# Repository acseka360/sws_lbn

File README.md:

# Lora Battery Node
## Solder WorkShop - *Advanced Track*

### PCB

Check out the PCB files with [Kicad 10](https://www.kicad.org/)

- Open the kicad\_pro project file
- Look at the schematic with the "Schematic Editor"
- Proceed to the "PCB editor" and push Alt-F3 to get into the 3D viewer

### Assembly

The interactive [BOM
webpage](https://htmlpreview.github.io/?https://github.com/acseka360/sws_lbn/blob/master/bom/ibom.html)
helps during assembly. You can mark components placed and check their exact
types.

### Bootloader

Initially a [J-Link](https://www.segger.com/products/debug-probes/j-link/) or
equivalent swd flasher is needed to load the bootloader on the virgin chip.

Use the *pca10056* type from the
[Adafruit](https://github.com/adafruit/Adafruit_nRF52_Bootloader/releases) repo.

### Firmware

You will need [PlatformIO](https://platformio.org/) to compile and install it.

First the bootstrapping firmware is needed, to set the IO voltages to 3.3V
permanently from the default 1.8V.

Then you can get the upstream
[Meshtastic](https://github.com/meshtastic/firmware) repo, that you should merge 
into the firmware folder, where our custom variant files already describe the 
board.

### 3D printed case

[Freecad 1.1](https://www.freecad.org/) made the 3d printed case files.

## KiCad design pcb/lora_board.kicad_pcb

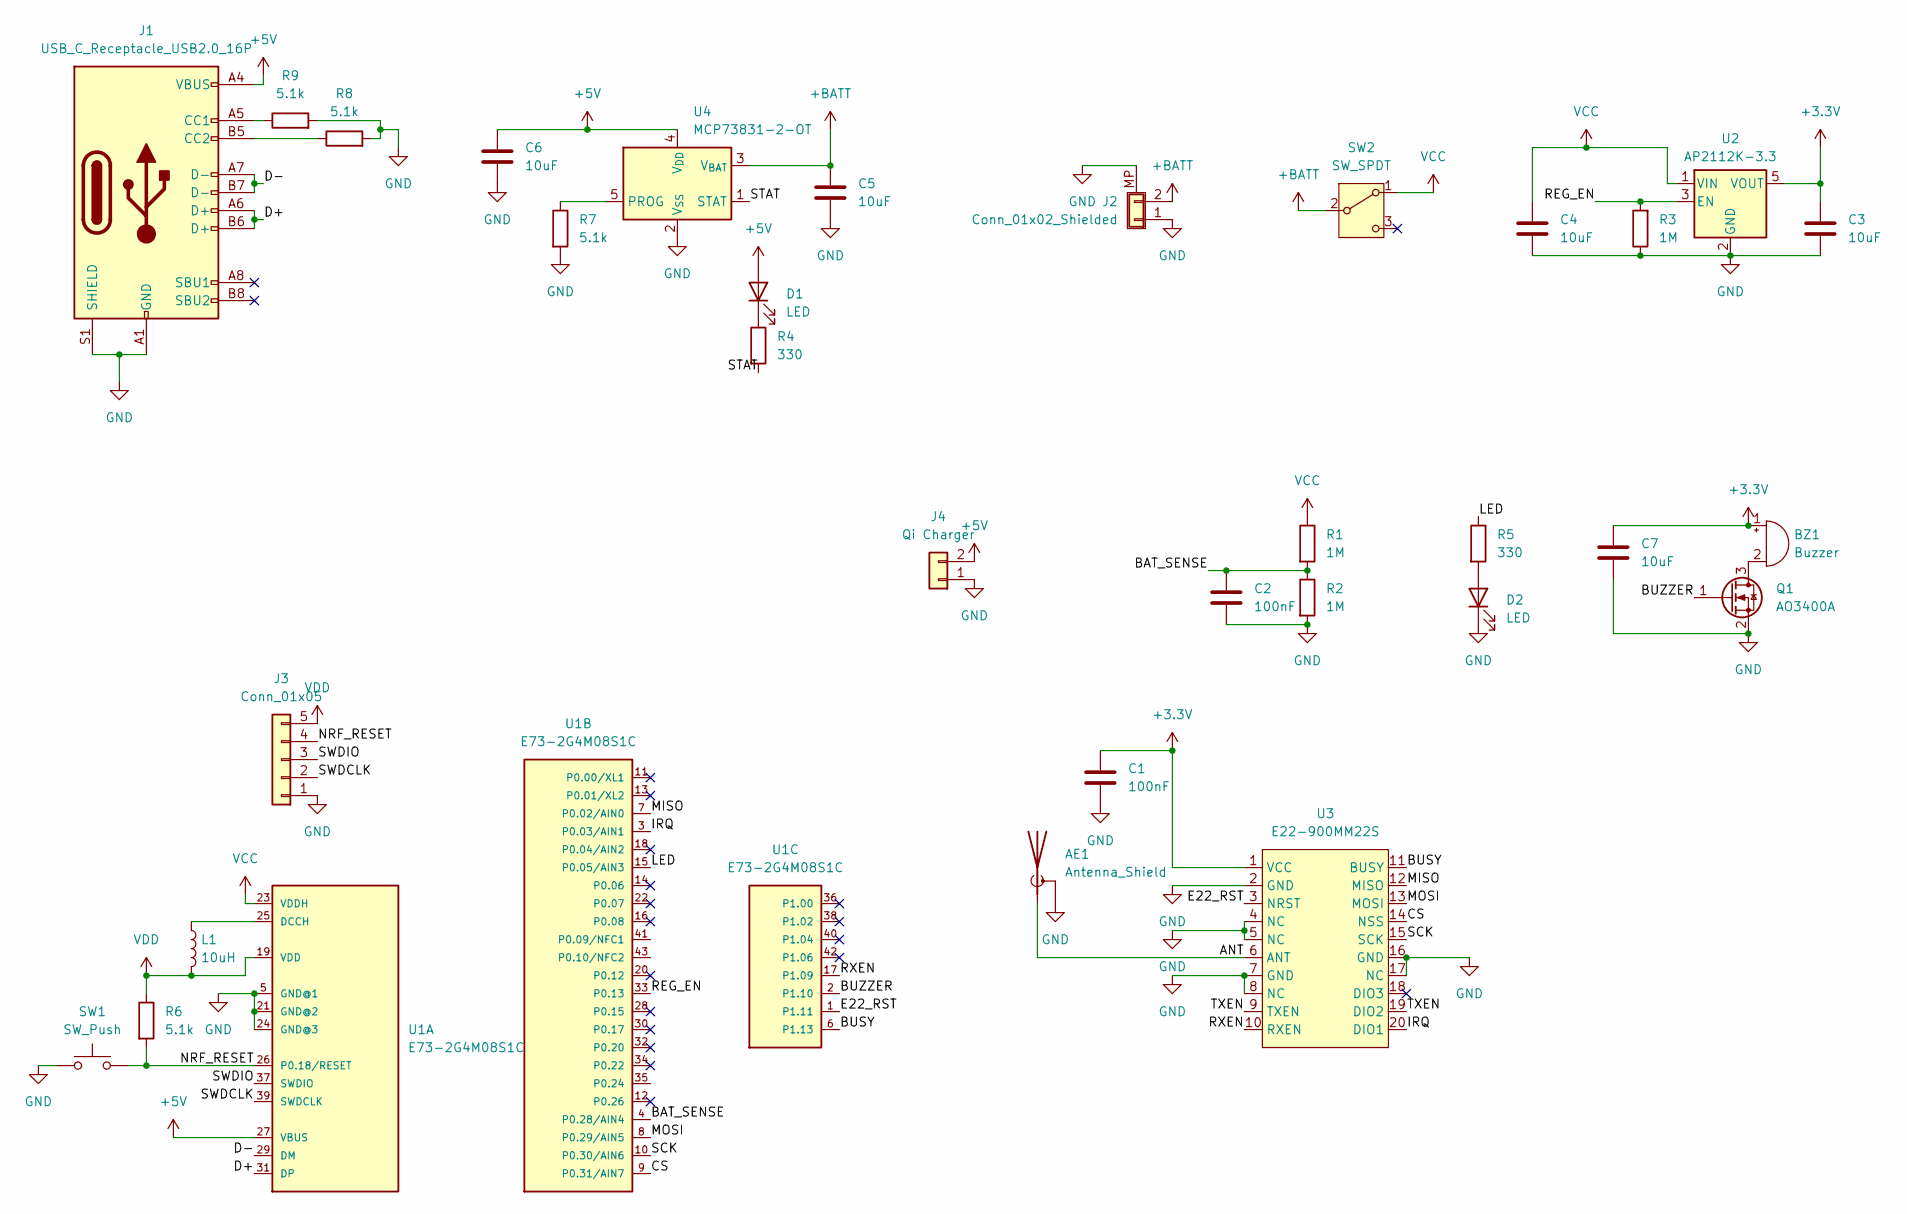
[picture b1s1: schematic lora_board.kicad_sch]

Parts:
AE1: Antenna_Shield; SMA_Amphenol_132289_EdgeMount
BZ1: Buzzer; MLT-5020
C1, C2: 100nF; C_0402_1005Metric_Pad0.74x0.62mm_HandSolder
C3, C4, C5, C6, C7: 10uF; C_0603_1608Metric_Pad1.08x0.95mm_HandSolder
D1, D2: LED; LED_0603_1608Metric_Pad1.05x0.95mm_HandSolder
J1: USB_C_Receptacle_USB2.0_16P; USB_C_Receptacle_GCT_USB4105-xx-A_16P_TopMnt_Horizontal
J2: Conn_01x02_Shielded; JST_SH_SM02B-SRSS-TB_1x02-1MP_P1.00mm_Horizontal
J3: Conn_01x05; PinHeader_1x05_P2.54mm_Vertical
J4: Qi Charger; QiCharger
L1: 10uH; L_0603_1608Metric_Pad1.05x0.95mm_HandSolder
Q1: AO3400A; SOT-23_Handsoldering
R1, R2, R3: 1M; R_0603_1608Metric_Pad0.98x0.95mm_HandSolder
R4, R5: 330; R_0603_1608Metric_Pad0.98x0.95mm_HandSolder
R6, R7, R8, R9: 5.1k; R_0603_1608Metric_Pad0.98x0.95mm_HandSolder
SW1: SW_Push; SW_SPST_B3U-1000P
SW2: SW_SPDT; SW_SPDT_PCM12
U1: E73-2G4M08S1C
U2: AP2112K-3.3; SOT-23-5_HandSoldering
U3: E22-900MM22S
U4: MCP73831-2-OT; SOT-23-5_HandSoldering

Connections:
+3.3V: BZ1.1 (+), C1.1, C3.1, C7.1, U2.5 (VOUT), U3.1 (VCC)
+5V: C6.1, D1.2 (A), J1.A4 (VBUS), J1.A9 (VBUS), J1.B4 (VBUS), J1.B9 (VBUS), J4.2, U1.27 (VBUS), U4.4 (V_{DD})
+BATT: C5.1, J2.2, SW2.2 (B), U4.3 (V_{BAT})
/ANT: AE1.1 (A), U3.6 (ANT)
/BAT_SENSE: C2.1, R1.2, R2.1, U1.4 (P0.28/AIN4)
/BUSY: U1.6 (P1.13), U3.11 (BUSY)
/BUZZER: Q1.1 (G), U1.2 (P1.10)
/CS: U1.9 (P0.31/AIN7), U3.14 (NSS)
/D+: J1.A6 (D+), J1.B6 (D+), U1.31 (DP)
/D-: J1.A7 (D-), J1.B7 (D-), U1.29 (DM)
/E22_RST: U1.1 (P1.11), U3.3 (NRST)
/IRQ: U1.3 (P0.03/AIN1), U3.20 (DIO1)
/LED: R5.1, U1.15 (P0.05/AIN3)
/MISO: U1.7 (P0.02/AIN0), U3.12 (MISO)
/MOSI: U1.8 (P0.29/AIN5), U3.13 (MOSI)
/NRF_RESET: J3.4, R6.2, SW1.2, U1.26 (P0.18/RESET)
/REG_EN: R3.2, U1.33 (P0.13), U2.3 (EN)
/RXEN: U1.17 (P1.09), U3.10 (RXEN)
/SCK: U1.10 (P0.30/AIN6), U3.15 (SCK)
/STAT: R4.2, U4.1 (STAT)
/SWDCLK: J3.2, U1.39 (SWDCLK)
/SWDIO: J3.3, U1.37 (SWDIO)
/TXEN: U3.9 (TXEN), U3.19 (DIO2)
GND: AE1.2 (Shield), C1.2, C2.2, C3.2, C4.2, C5.2, C6.2, C7.2, D2.1 (K), J1.A1 (GND), J1.A12 (GND), J1.B1 (GND), J1.B12 (GND), J1.S1 (SHIELD), J2.1, J2.MP (Shield), J3.1, J4.1, Q1.2 (S), R2.2, R3.1, R7.2, R8.2, R9.2, SW1.1, U1.5 (GND@1), U1.21 (GND@2), U1.24 (GND@3), U2.2 (GND), U3.2 (GND), U3.4 (NC), U3.5 (NC), U3.7 (GND), U3.8 (NC), U3.16 (GND), U3.17 (NC), U4.2 (V_{SS})
unnamed: BZ1.2 (-), Q1.3 (D)
unnamed: D1.1 (K), R4.1
unnamed: D2.2 (A), R5.2
unnamed: J1.A5 (CC1), R9.1
unnamed: J1.B5 (CC2), R8.1
unnamed: L1.1, U1.25 (DCCH)
unnamed: R7.1, U4.5 (PROG)
VCC: C4.1, R1.1, SW2.1 (A), U1.23 (VDDH), U2.1 (VIN)
VDD: J3.5, L1.2, R6.1, U1.19 (VDD)

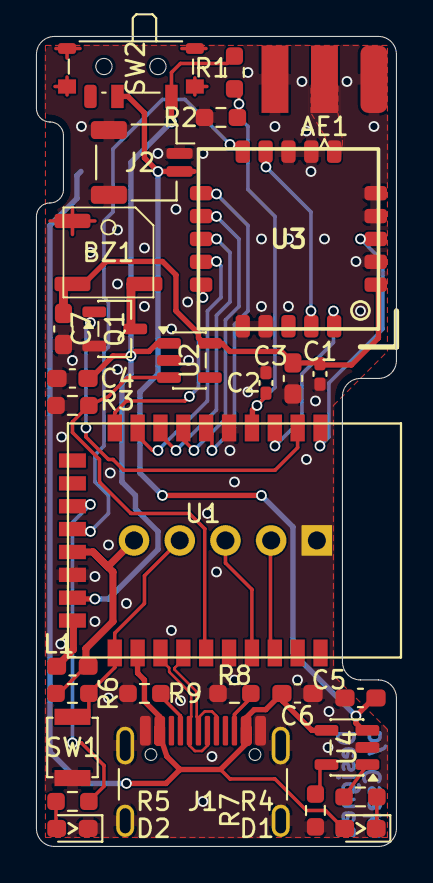
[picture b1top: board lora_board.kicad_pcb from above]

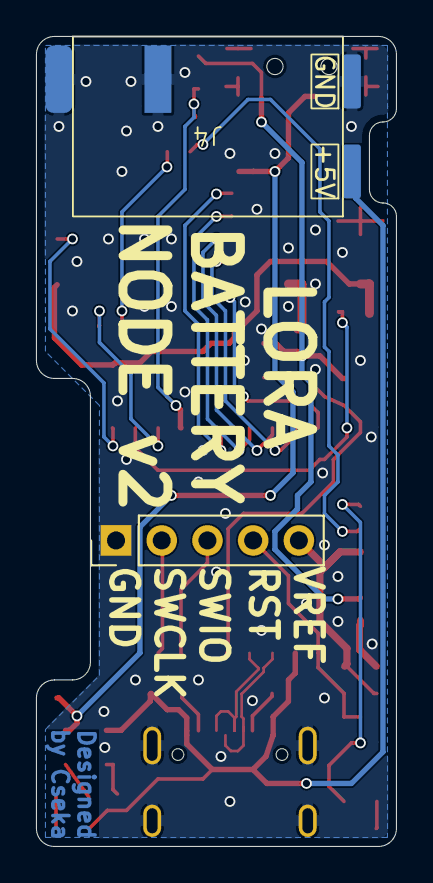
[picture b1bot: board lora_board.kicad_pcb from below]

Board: 2 copper layers, 20.0 x 45.0 mm, 32 parts (2 on the bottom side), 33 nets.

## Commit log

2026-02-12 ordered v1
2026-03-08 pre del
2026-03-14 pre del esp32-s3-supermini
2026-04-02 small ordered v1
2026-04-04 v2 rc1
2026-04-06 v2 rc2
2026-04-06 proper subfolders
2026-04-06 readme added
2026-04-07 variant added, with bootstrap
2026-04-07 v2 rc3
2026-04-14 ordered v2
2026-05-23 working firmware on v2
2026-05-25 case uploaded, and updated readme
